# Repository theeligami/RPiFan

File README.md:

# RPiFan
A PWM fan speed controller for the raspberry pi.

## Getting started
These instructions will get you the latest version of the RPiFan fan control script installed. It will also add and activate a system service for to run the script automatically.

The repository also includes a [kicad](https://kicad-pcb.org/) project file so you can order the pcb from a manufacturer or design your own.
### Prerequisites
You need a working version of Raspberry Pi OS (formerly Raspbian) on your raspberry pi. You can get the latest version of Raspberry Pi OS [here](https://www.raspberrypi.org/downloads/).

Other debian-based distributions might work too, but are not officially supported by RPiFan.
### Connecting the pcb

*[Original Image by Efa](https://commons.wikimedia.org/wiki/File:Raspberry_Pi_Zero_-_Location_of_connectors_and_ICs.svg) licensed under the [creative commons Attribution-ShareAlike 3.0](https://creativecommons.org/licenses/by-sa/3.0/legalcode)*

### Installing
Clone the repository to your raspberry pi.
```
git clone https://github.com/theeligami/RPiFan.git
```
Go to the directory of the install script
```
cd ./RPiFan/src
```
Mark the install script as executable
```
chmod +x install.sh
```
Run the install script as root
```
sudo ./install.sh
```

### Uninstalling
Mark the uninstall script as executable
```
sudo chmod +x /usr/local/sbin/RPiFan/uninstall.sh
```
Run the uninstall script
```
sudo /usr/local/sbin/RPiFan/uninstall.sh
```

## License

This project is licensed under the GPL 3.0 - see the [LICENSE.md](LICENSE.md) file for details

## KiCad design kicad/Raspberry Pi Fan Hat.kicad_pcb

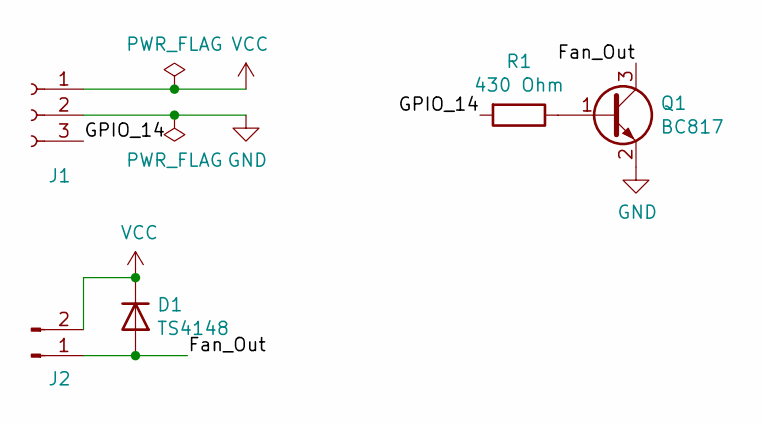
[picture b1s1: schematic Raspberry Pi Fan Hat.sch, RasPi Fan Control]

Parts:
D1: TS4148; R_0603_1608Metric_Pad1.05x0.95mm_HandSolder
J1: Conn_01x03_Female; PinSocket_1x03_P2.54mm_Vertical
J2: Conn_01x02_Male; PinHeader_1x02_P2.54mm_Horizontal
Q1: BC817; SOT-23
R1: 430 Ohm; R_0805_2012Metric_Pad1.15x1.40mm_HandSolder

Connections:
/Fan_Out: D1.2 (A), J2.1, Q1.3 (C)
/GPIO_14: J1.3, R1.2
GND: J1.2, Q1.2 (E)
unnamed: Q1.1 (B), R1.1
VCC: D1.1 (K), J1.1, J2.2

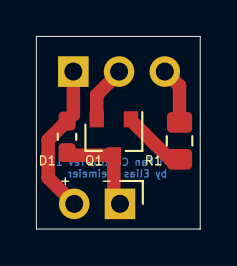
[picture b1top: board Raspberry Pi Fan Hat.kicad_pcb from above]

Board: 2 copper layers, 9.1 x 10.7 mm, 5 parts (1 on the bottom side), 5 nets.

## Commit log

2020-06-22 Zipped gerbers
2020-06-23 Added datasheets
2020-06-23 Added fan control script
2020-06-23 Added system service. Changend name of main.
2020-06-23 Removed if __name__='__main__'
2020-06-23 Finished RPiFan.service
2020-06-24 Finished install script
2020-06-25 Added data for kicost
2020-06-25 Adjustet pwm duty cycle
2020-06-25 Made the code nicer
2020-06-25 Removed bad BOM csv
2020-06-26 Added uninstall script
2020-06-26 Added opt out for installation
2020-07-02 Corrected if-statements; added python3-pip to dependencies
2020-07-02 Corrected if-statements (fuck bash-syntax lol)
2020-07-02 Fixed typo
2020-07-02 Fixed typos. Also too dumb for python syntax. Fuck decimal points.
2020-07-02 get_temp now returns a float
2020-07-02 Added dir for uninstall script
2020-07-03 Create LICENSE
2020-07-03 Rename LICENSE to LICENSE.md
2020-07-03 Removed redundancy
2020-07-03 Added doc directory and example image for connecting
2020-07-03 Added graphics for pcb connection
2020-07-04 Added comments
2020-07-04 Added variable for PWM frequency
2020-07-04 Changed README
2020-07-04 Added .gitignore
2020-07-04 Removed backups from versioning
2020-07-04 Formatting
2020-07-27 Fixed pip install for older versions of pip3
